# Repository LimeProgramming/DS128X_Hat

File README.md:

# DS128X_Hat
Replace your dead Dallas RTC chip with a DS1285/DS12885 with an added hat for a battery and crystal OR use the hat to make a repaired Dallas RTC chip look a bit nicer.

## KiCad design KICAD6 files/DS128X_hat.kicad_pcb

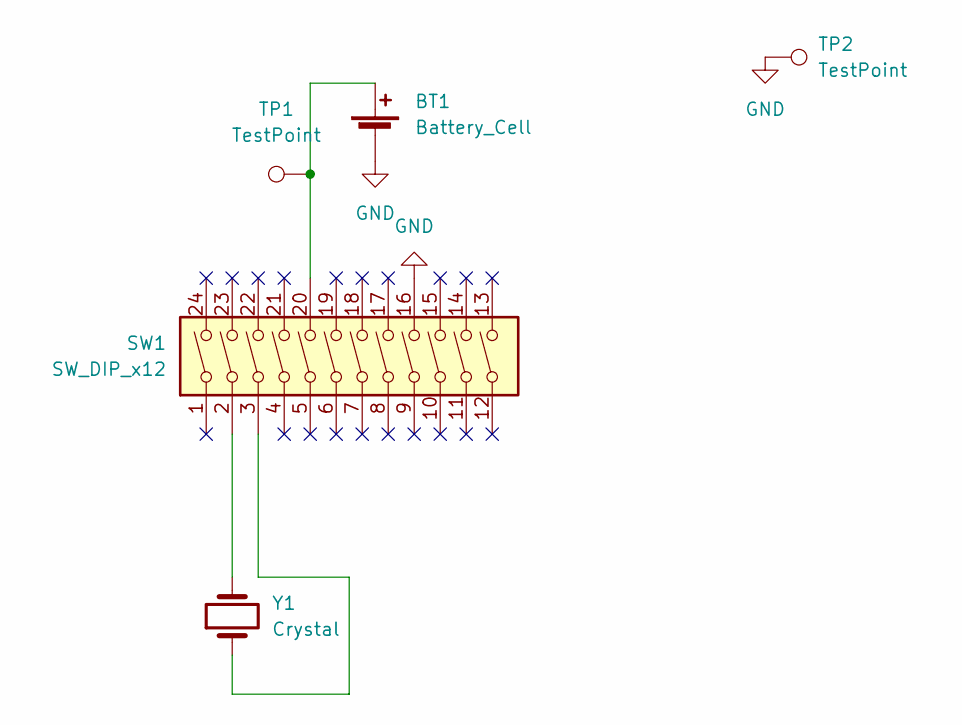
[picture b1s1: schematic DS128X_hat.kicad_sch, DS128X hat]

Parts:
BT1: Battery_Cell; CR1220
SW1: SW_DIP_x12; SMDIP-24_W11.48mm
TP1: TestPoint; bat_pad_pos_D2.0mm
TP2: TestPoint; bat_pad_neg_D2.0mm
Y1: Crystal; Crystal_C26-LF_D2.1mm_L6.5mm_Horizontal

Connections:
GND: BT1.2 (-), SW1.16, TP2.1
unnamed: BT1.1 (+), SW1.20, TP1.1
unnamed: SW1.2, Y1.2
unnamed: SW1.3, Y1.1

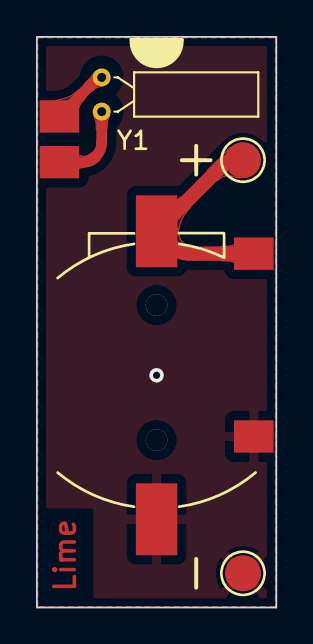
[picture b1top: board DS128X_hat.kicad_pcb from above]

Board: 2 copper layers, 13.3 x 31.7 mm, 5 parts (0 on the bottom side), 4 nets.
